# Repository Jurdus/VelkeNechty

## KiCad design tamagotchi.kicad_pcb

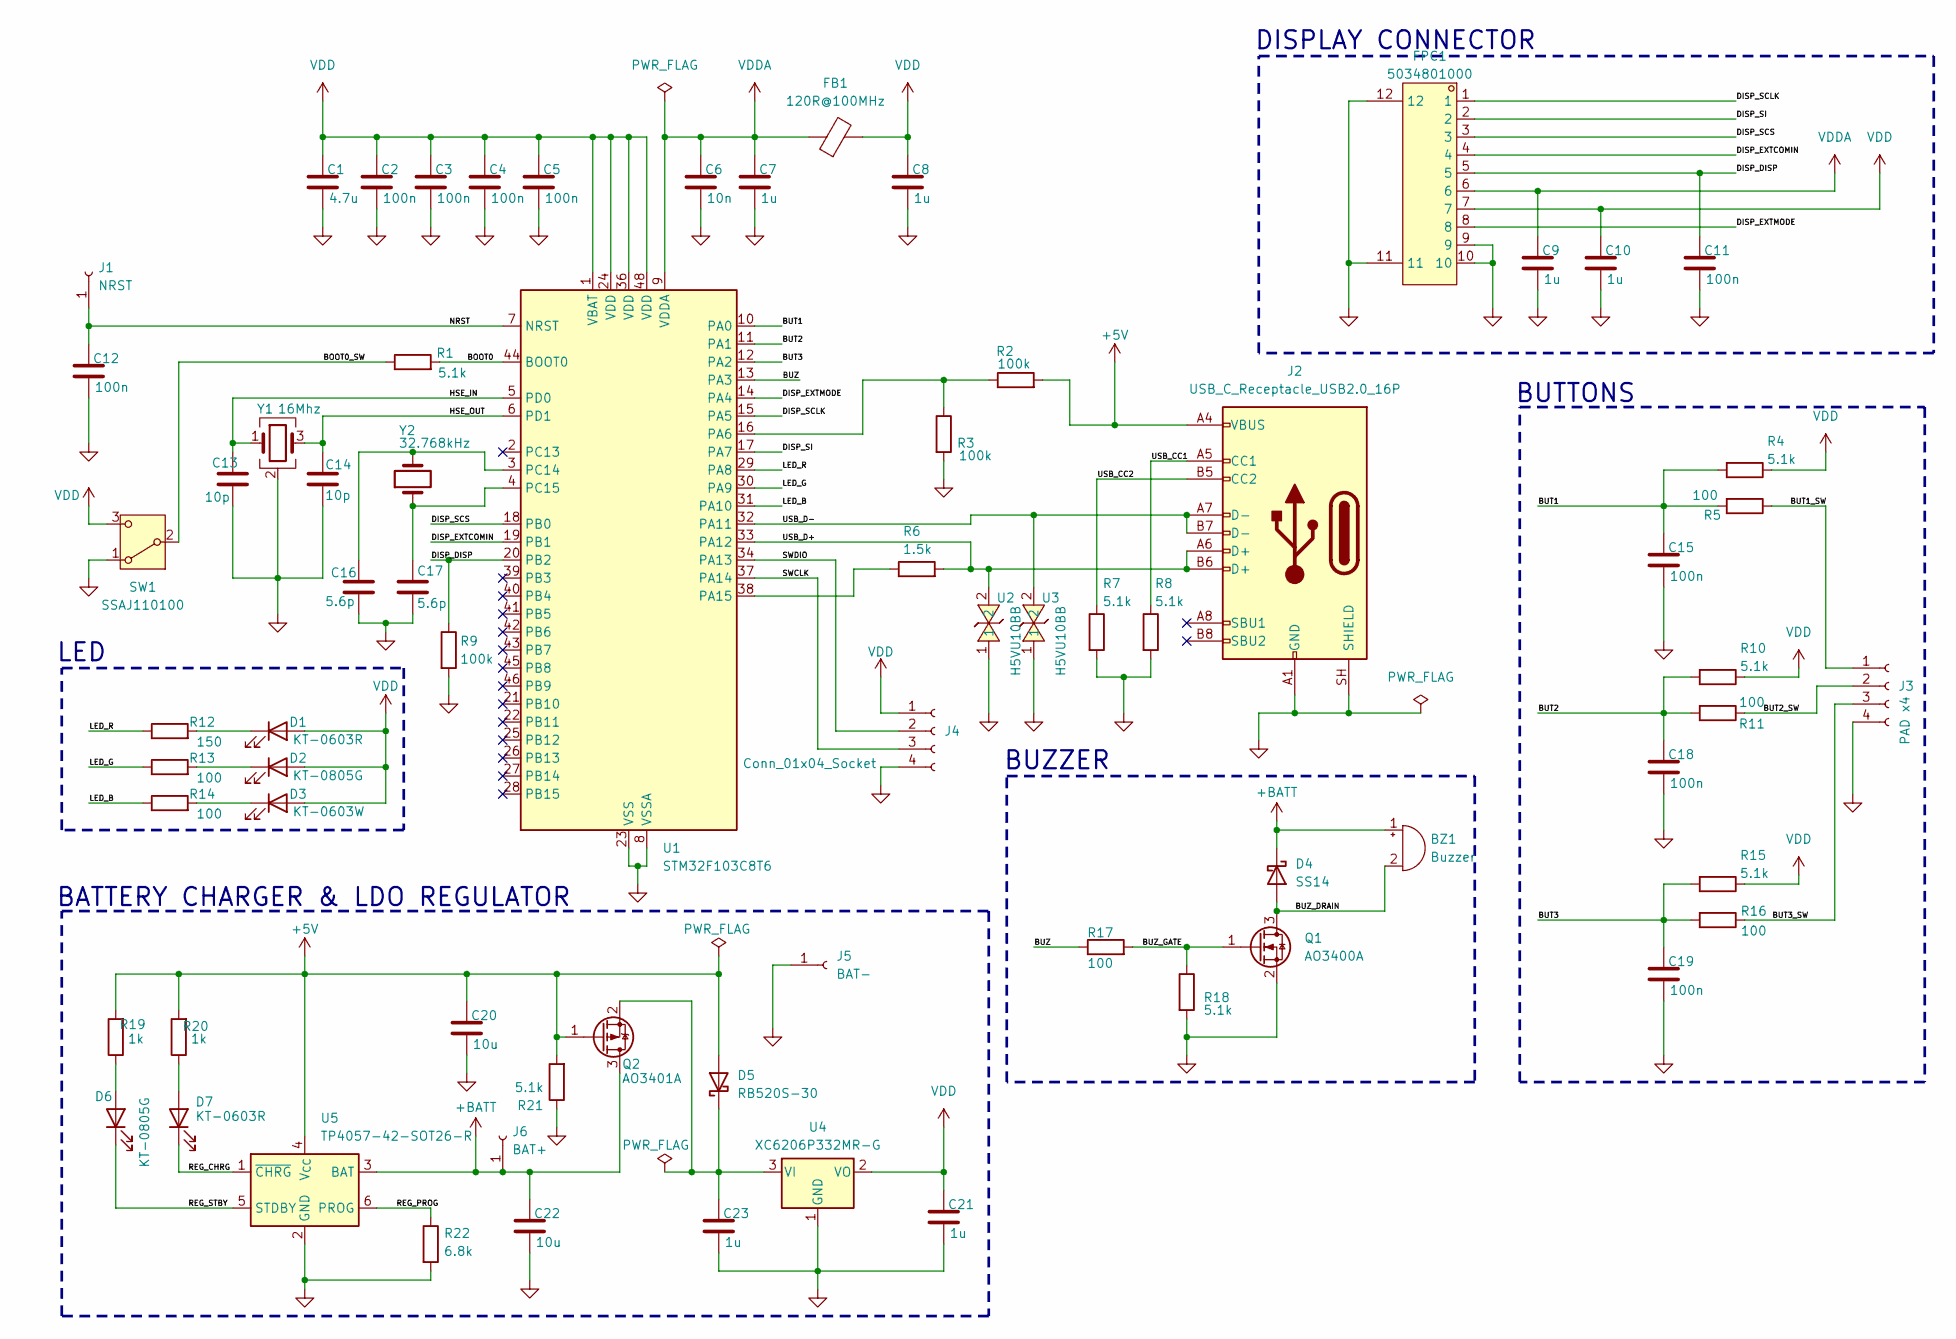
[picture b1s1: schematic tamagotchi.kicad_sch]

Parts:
BZ1: Buzzer; PinSocket_1x02_P2.54mm_Vertical
C1: 4.7u; C_0402_1005Metric; LCSC Part C23733
C2, C3, C4, C5, C11, C12, C15, C18, C19: 100n; C_0402_1005Metric; LCSC C1525
C6: 10n; C_0402_1005Metric; LCSC Part C15195
C7, C8, C9, C10, C21, C23: 1u; C_0402_1005Metric; LCSC Part C52923
C13, C14: 10p; C_0402_1005Metric; LCSC Part C32949
C16, C17: 5.6p; C_0402_1005Metric; LCSC Part C30274
C20, C22: 10u; C_0603_1608Metric; LCSC Part C96446
D1, D7: KT-0603R; LED_0603_1608Metric; LCSC Part C2286
D2, D6: KT-0805G; LED_0805_2012Metric; LCSC Part C2297
D3: KT-0603W; LED_0603_1608Metric; LCSC Part C2290
D4: SS14; D_SMA; LCSC Part C2480
D5: RB520S-30; D_SOD-523; LCSC Part C7502701
FB1: 120R@100MHz; L_0603_1608Metric; LCSC C14709
FPC1: 5034801000; FPC-SMD_5034801000; LCSC Part C127355
J1: NRST; PinHeader_1x01_P2.54mm_Vertical
J2: USB_C_Receptacle_USB2.0_16P; USB_C_Receptacle_HCTL_HC-TYPE-C-16P-01A; LCSC C2894897
J3: PAD x4; PinSocket_1x04_P2.54mm_Vertical
J4: Conn_01x04_Socket; PinSocket_1x04_P2.54mm_Vertical
J5: BAT-; PinHeader_1x01_P2.54mm_Vertical
J6: BAT+; PinHeader_1x01_P2.54mm_Vertical
Q1: AO3400A; SOT-23; LCSC Part C20917
Q2: AO3401A; SOT-23; LCSC Part C15127
R1, R4, R7, R8, R10, R15, R18, R21: 5.1k; R_0603_1608Metric; LCSC Part C23186
R2, R3, R9: 100k; R_0402_1005Metric; LCSC Part C25741
R5, R11, R13, R14, R16, R17: 100; R_0603_1608Metric; LCSC Part C22775
R6: 1.5k; R_0402_1005Metric; LCSC Part C25867
R12: 150; R_0603_1608Metric; LCSC Part C22808
R19, R20: 1k; R_0603_1608Metric; LCSC Part C21190
R22: 6.8k; R_0603_1608Metric; LCSC Part C23212
SW1: SSAJ110100; SW-SMD_SSAJ110100; LCSC Part C160863
U1: STM32F103C8T6; LQFP-48_7x7mm_P0.5mm; LCSC Part C8734
U2, U3: H5VU10BB; DFN1006-2L-BI; LCSC Part C20615786
U4: XC6206P332MR-G; SOT-23-3; LCSC Part C5446
U5: TP4057-42-SOT26-R; SOT-23-6; LCSC Part C12044
Y1: 16Mhz; Crystal_SMD_3225-4Pin_3.2x2.5mm; LCSC C13738
Y2: 32.768kHz; Crystal_SMD_3215-2Pin_3.2x1.5mm; LCSC Part C94673

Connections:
+5V: C20.1, D5.2 (A), J2.A4 (VBUS), J2.A9 (VBUS), J2.B4 (VBUS), J2.B9 (VBUS), Q2.1 (G), R2.2, R19.2, R20.2, R21.2, U5.4 (V_{CC})
+BATT: BZ1.1 (+), C22.1, D4.1 (K), J6.1 (Pin_1_1), Q2.3 (D), U5.3 (BAT)
/BOOT0: R1.2, U1.44 (BOOT0)
/BOOT0_SW: R1.1, SW1.2 (B)
/BUT1: C15.1, R4.2, R5.2, U1.10 (PA0)
/BUT1_SW: J3.1, R5.1
/BUT2: C18.1, R10.2, R11.2, U1.11 (PA1)
/BUT2_SW: J3.2, R11.1
/BUT3: C19.1, R15.2, R16.2, U1.12 (PA2)
/BUT3_SW: J3.3, R16.1
/BUZ: R17.1, U1.13 (PA3)
/BUZ_DRAIN: BZ1.2 (-), D4.2 (A), Q1.3 (D)
/BUZ_GATE: Q1.1 (G), R17.2, R18.1
/DISP_DISP: C11.1, FPC1.5, R9.1, U1.20 (PB2)
/DISP_EXTCOMIN: FPC1.4, U1.19 (PB1)
/DISP_EXTMODE: FPC1.8, U1.14 (PA4)
/DISP_SCLK: FPC1.1, U1.15 (PA5)
/DISP_SCS: FPC1.3, U1.18 (PB0)
/DISP_SI: FPC1.2, U1.17 (PA7)
/HSE_IN: C13.1, U1.5 (PD0), Y1.1
/HSE_OUT: C14.1, U1.6 (PD1), Y1.3
/LED_B: R14.1, U1.31 (PA10)
/LED_G: R13.1, U1.30 (PA9)
/LED_R: R12.1, U1.29 (PA8)
/NRST: C12.1, J1.1 (Pin_1_1), U1.7 (NRST)
/REG_CHRG: D7.1 (K), U5.1 (~CHRG)
/REG_PROG: R22.1, U5.6 (PROG)
/REG_STBY: D6.1 (K), U5.5 (STDBY)
/SWCLK: J4.3, U1.37 (PA14)
/SWDIO: J4.2, U1.34 (PA13)
/USB_CC1: J2.A5 (CC1), R8.1
/USB_CC2: J2.B5 (CC2), R7.1
/USB_D+: J2.A6 (D+), J2.B6 (D+), R6.2, U1.33 (PA12), U2.2
/USB_D-: J2.A7 (D-), J2.B7 (D-), U1.32 (PA11), U3.2
GND: C1.2, C2.2, C3.2, C4.2, C5.2, C6.2, C7.2, C8.2, C9.2, C10.2, C11.2, C12.2, C13.2, C14.2, C15.2, C16.2, C17.2, C18.2, C19.2, C20.2, C21.2, C22.2, C23.2, FPC1.9, FPC1.10, FPC1.11, FPC1.12, J2.A1 (GND), J2.A12 (GND), J2.B1 (GND), J2.B12 (GND), J2.SH (SHIELD), J3.4, J4.4, J5.1 (Pin_1_1), Q1.2 (S), R3.2, R7.2, R8.2, R9.2, R18.2, R21.1, R22.2, SW1.1 (A), U1.8 (VSSA), U1.23 (VSS), U1.35 (VSS), U1.47 (VSS), U2.1, U3.1, U4.1 (GND), U5.2 (GND), Y1.2 (G), Y1.4 (G)
unnamed: D1.1 (K), R12.2
unnamed: D2.1 (K), R13.2
unnamed: D3.1 (K), R14.2
unnamed: C23.1, D5.1 (K), Q2.2 (S), U4.3 (VI)
unnamed: D6.2 (A), R19.1
unnamed: D7.2 (A), R20.1
unnamed: R2.1, R3.1, U1.16 (PA6)
unnamed: R6.1, U1.38 (PA15)
unnamed: C16.1, U1.3 (PC14), Y2.2
unnamed: C17.1, U1.4 (PC15), Y2.1
VDD: C1.1, C2.1, C3.1, C4.1, C5.1, C8.1, C10.1, C21.1, D1.2 (A), D2.2 (A), D3.2 (A), FB1.2, FPC1.7, J4.1, R4.1, R10.1, R15.1, SW1.3 (C), U1.1 (VBAT), U1.24 (VDD), U1.36 (VDD), U1.48 (VDD), U4.2 (VO)
VDDA: C6.1, C7.1, C9.1, FB1.1, FPC1.6, U1.9 (VDDA)

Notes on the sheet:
BUZZER
BUTTONS
BATTERY CHARGER & LDO REGULATOR
DISPLAY CONNECTOR
LED

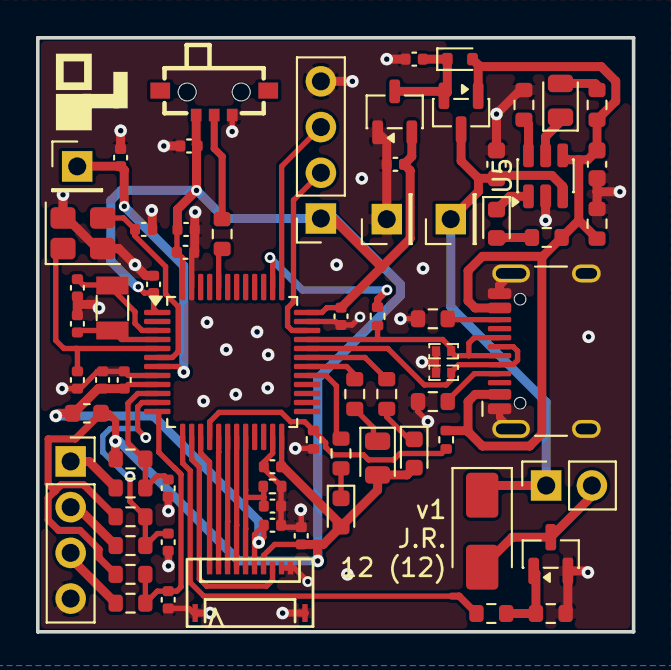
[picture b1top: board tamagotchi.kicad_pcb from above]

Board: 2 copper layers, 33.1 x 33.0 mm, 71 parts (0 on the bottom side), 47 nets.

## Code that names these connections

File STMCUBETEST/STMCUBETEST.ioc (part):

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Mcu.Name=STM32F103C(8-B)Tx
Mcu.Package=LQFP48
Mcu.UserName=STM32F103C8Tx
PA0-WKUP.GPIOParameters=GPIO_Label
PA0-WKUP.GPIO_Label=BUT1
PA0-WKUP.Signal=GPIO_Input
PA1.GPIOParameters=GPIO_Label
PA1.GPIO_Label=BUT2
PA1.Signal=GPIO_Input
PA10.Signal=S_TIM1_CH3
PA13.Mode=Serial_Wire
PA13.Signal=SYS_JTMS-SWDIO
PA14.Mode=Serial_Wire
PA14.Signal=SYS_JTCK-SWCLK
PA15.GPIOParameters=PinState
PA15.PinState=GPIO_PIN_SET
PA15.Signal=GPIO_Output
PA2.GPIOParameters=GPIO_Label
PA2.GPIO_Label=BUT3
PA2.Signal=GPIO_Input
PA4.GPIOParameters=GPIO_Speed,GPIO_Label
PA4.GPIO_Label=DISP_EXTMODE
PA4.GPIO_Speed=GPIO_SPEED_FREQ_HIGH
PA4.Signal=GPIO_Output
PA5.GPIOParameters=GPIO_Speed,GPIO_Label
PA5.GPIO_Label=DISP_SCLK
PA5.GPIO_Speed=GPIO_SPEED_FREQ_HIGH
PA5.Signal=GPIO_Output
PA7.GPIOParameters=GPIO_Speed,GPIO_Label
PA7.GPIO_Label=DISP_SI
PA7.GPIO_Speed=GPIO_SPEED_FREQ_HIGH
PA7.Signal=GPIO_Output
PA8.Signal=S_TIM1_CH1
PA9.Signal=S_TIM1_CH2
PB0.GPIOParameters=GPIO_Speed,GPIO_Label
PB0.GPIO_Label=DISP_SCS
PB0.GPIO_Speed=GPIO_SPEED_FREQ_HIGH
PB0.Signal=GPIO_Output
PB1.GPIOParameters=GPIO_Speed,GPIO_Label
PB1.GPIO_Label=DISP_EXTCOMIN
PB1.GPIO_Speed=GPIO_SPEED_FREQ_HIGH
PB1.Signal=GPIO_Output
PB2.GPIOParameters=GPIO_Speed,GPIO_Label
PB2.GPIO_Label=DISP_DISP
PB2.GPIO_Speed=GPIO_SPEED_FREQ_HIGH
PB2.Signal=GPIO_Output
PC14-OSC32_IN.Mode=LSE-External-Oscillator
PC14-OSC32_IN.Signal=RCC_OSC32_IN
PC15-OSC32_OUT.Mode=LSE-External-Oscillator
PC15-OSC32_OUT.Signal=RCC_OSC32_OUT
PD0-OSC_IN.Mode=HSE-External-Oscillator
PD0-OSC_IN.Signal=RCC_OSC_IN
PD1-OSC_OUT.Mode=HSE-External-Oscillator
PD1-OSC_OUT.Signal=RCC_OSC_OUT
RCC.HSEDivPLL=RCC_HSE_PREDIV_DIV2
RCC.HSE_VALUE=16000000
RCC.SYSCLKFreq_VALUE=72000000
RCC.SYSCLKSource=RCC_SYSCLKSOURCE_PLLCLK
board=custom

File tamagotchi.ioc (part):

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Mcu.Name=STM32F103C(8-B)Tx
Mcu.Package=LQFP48
Mcu.UserName=STM32F103C8Tx
PA0-WKUP.Signal=GPIO_Input
PA1.Signal=GPIO_Input
PA10.Signal=S_TIM1_CH3
PA11.Mode=Device
PA11.Signal=USB_DM
PA12.Mode=Device
PA12.Signal=USB_DP
PA13.Mode=Serial_Wire
PA13.Signal=SYS_JTMS-SWDIO
PA14.Mode=Serial_Wire
PA14.Signal=SYS_JTCK-SWCLK
PA15.Signal=S_TIM2_CH1_ETR
PA2.Signal=GPIO_Input
PA5.Mode=TX_Only_Simplex_Unidirect_Master
PA5.Signal=SPI1_SCK
PA7.Mode=TX_Only_Simplex_Unidirect_Master
PA7.Signal=SPI1_MOSI
PA8.Signal=S_TIM1_CH1
PA9.Signal=S_TIM1_CH2
PB0.Signal=GPIO_Output
PB1.Signal=S_TIM3_CH4
PB10.Signal=GPIO_Output
PB2.Signal=GPIO_Output
PC14-OSC32_IN.Mode=LSE-External-Oscillator
PC14-OSC32_IN.Signal=RCC_OSC32_IN
PC15-OSC32_OUT.Mode=LSE-External-Oscillator
PC15-OSC32_OUT.Signal=RCC_OSC32_OUT
PD0-OSC_IN.Mode=HSE-External-Oscillator
PD0-OSC_IN.Signal=RCC_OSC_IN
PD1-OSC_OUT.Mode=HSE-External-Oscillator
PD1-OSC_OUT.Signal=RCC_OSC_OUT
RCC.HSE_VALUE=16000000
RCC.SYSCLKFreq_VALUE=16000000
RCC.SYSCLKSource=RCC_SYSCLKSOURCE_HSE
board=custom
